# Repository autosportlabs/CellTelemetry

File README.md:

CellTelemetry
=============

Realtime telemetry module for RaceCapture/Pro

http://www.autosportlabs.net/RaceCapture

See the License.txt file for more information on Licensing for this software.

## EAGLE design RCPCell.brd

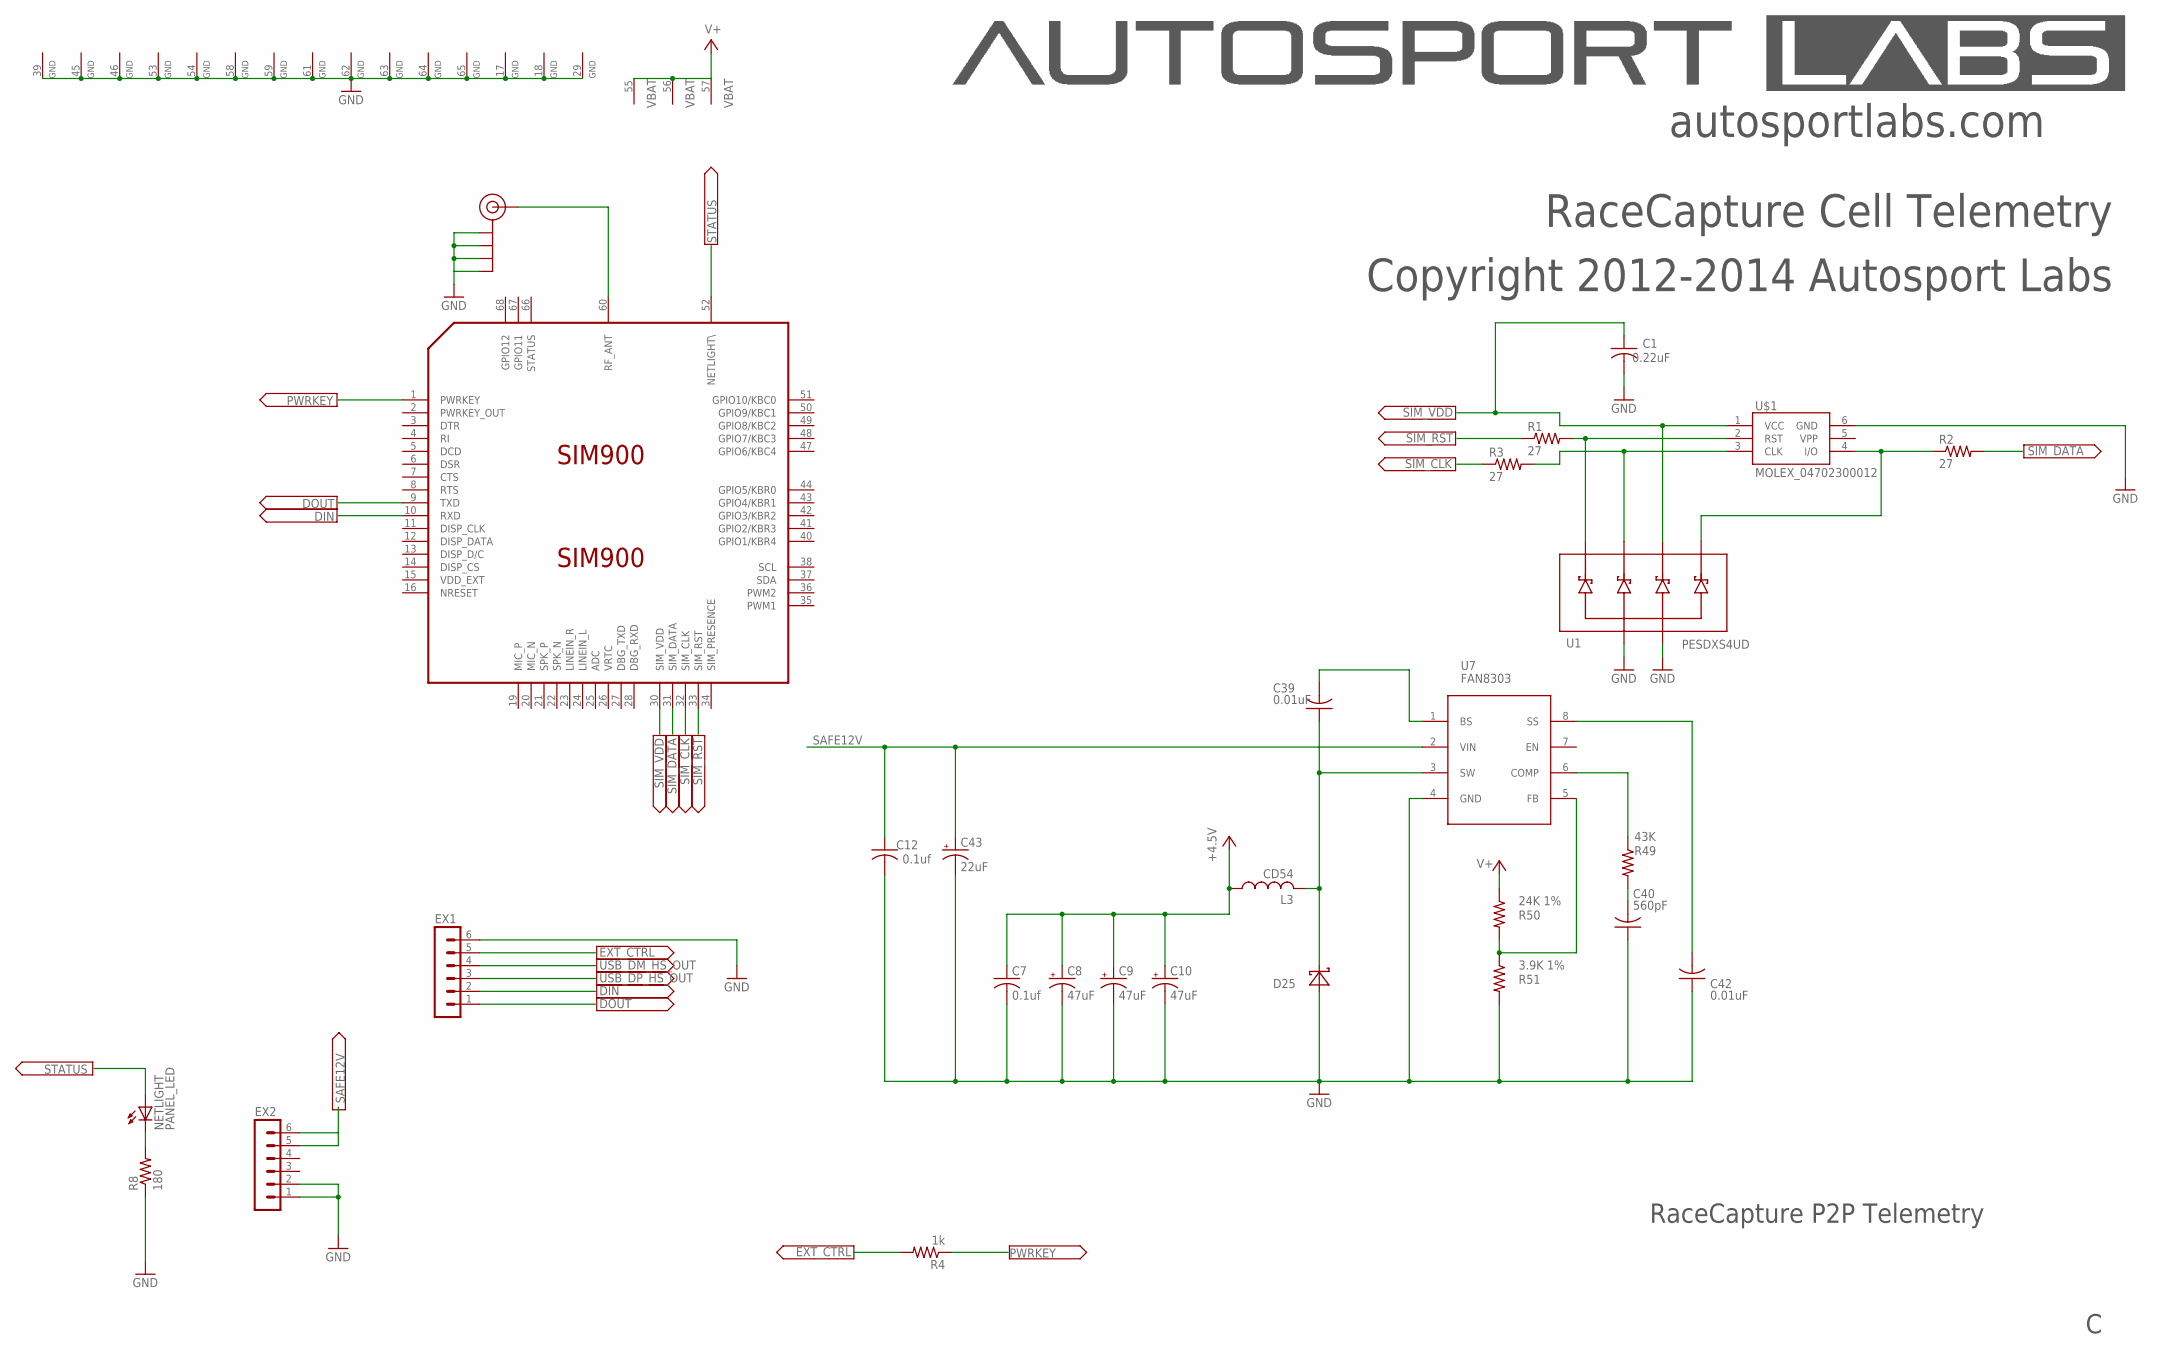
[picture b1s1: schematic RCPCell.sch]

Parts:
C1: 0.22uF; C0603
C7, C12: 0.1uf; C0603
C8, C9, C10: 47uF; SMC_D
C39, C42: 0.01uF; C0603
C40: 560pF; C0603
C43: 22uF; 153CLV-0605
D25: SCHOTTKY; SMA
EX1, EX2: MA06-1
J$1: SMA_EDGE; SMA-EDGE
L3: CD54
NETLIGHT: PANEL_LED; RIGHTANGLE_CML_5323F5
R1, R2, R3: 27; 0603
R4: 1k; 0603
R8: 180; 0603
R49: 43K; R0603
R50: 24K 1%; R0603
R51: 3.9K 1%; R0603
SIM900: SIM900
U1: PESDXS4UD; SC-74
U7: FAN8303; SO-8
U$1: MOLEX_04702300012; MOLEX_91228-3001

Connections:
DIN: EX1.2, SIM900.10 (RXD)
DOUT: EX1.1, SIM900.9 (TXD)
EXT_CTRL: EX1.5, R4.2
GND: C1.2, C7.2, C8.-, C9.-, C10.-, C12.2, C40.1, C42.1, C43.-, D25.A, EX1.6, EX2.1, EX2.2, J$1.GND@0 (GND), J$1.GND@1 (GND), J$1.GND@2 (GND), J$1.GND@3 (GND), R8.1, R51.2, SIM900.17 (GND), SIM900.18 (GND), SIM900.29 (GND), SIM900.39 (GND), SIM900.45 (GND), SIM900.46 (GND), SIM900.53 (GND), SIM900.54 (GND), SIM900.58 (GND), SIM900.59 (GND), SIM900.61 (GND), SIM900.62 (GND), SIM900.63 (GND), SIM900.64 (GND), SIM900.65 (GND), U1.2, U1.5, U7.4 (GND), U$1.6 (GND)
unnamed: NETLIGHT.C, R8.2
unnamed: R50.2, R51.1, U7.5 (FB)
unnamed: C39.2, U7.1 (BS)
unnamed: C39.1, D25.C, L3.P$2 (2), U7.3 (SW)
unnamed: C40.2, R49.2
unnamed: R49.1, U7.6 (COMP)
unnamed: C42.2, U7.8 (SS)
PWRKEY: R4.1, SIM900.1 (PWRKEY)
RF_ANT: J$1.SIG (SIGNAL), SIM900.60 (RF_ANT)
SAFE12V: C12.1, C43.+, EX2.5, EX2.6, U7.2 (VIN)
SIM_CLK: R3.1, SIM900.32 (SIM_CLK)
SIM_CLK_CARD: R3.2, U1.3, U$1.3 (CLK)
SIM_DATA: R2.2, SIM900.31 (SIM_DATA)
SIM_DATA_CARD: R2.1, U1.6, U$1.4 (I/O)
SIM_RST: R1.1, SIM900.33 (SIM_RST)
SIM_RST_CARD: R1.2, U1.1, U$1.2 (RST)
SIM_VDD: C1.1, SIM900.30 (SIM_VDD), U1.4, U$1.1 (VCC)
STATUS: NETLIGHT.A, SIM900.52 (NETLIGHT\)
USB_DM_HS_OUT: EX1.4
USB_DP_HS_OUT: EX1.3
V+: C7.1, C8.+, C9.+, C10.+, L3.P$1 (1), R50.1, SIM900.55 (VBAT), SIM900.56 (VBAT), SIM900.57 (VBAT)

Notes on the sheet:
RaceCapture P2P Telemetry
Copyright 2012-2014 Autosport Labs
RaceCapture Cell Telemetry
autosportlabs.com

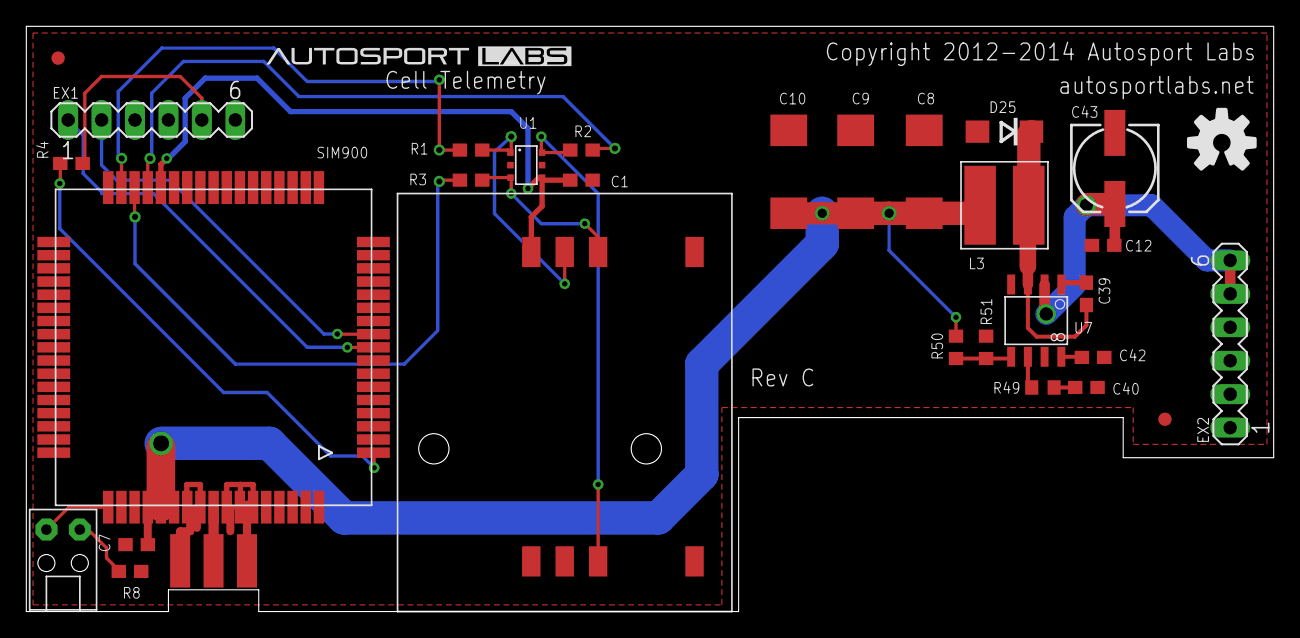
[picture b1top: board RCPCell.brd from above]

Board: 2 copper layers, 94.7 x 44.5 mm, 28 parts (0 on the bottom side), 23 nets.

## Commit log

2012-08-18 added Cellular telemetry module
2012-08-18 added current limiting resistors to TVS circuit
2012-08-18 final update before expert review
2012-08-19 changed design around SMA connector, designe for 50 ohms at 900MHz
2013-03-14 updates to final RCP cell device
2013-03-14 updated cellular module with additional RX-TX LEDs, new simcard holder, removed STATUS light b/c not functional on SIM900
2013-03-14 bumped to RevB
2013-04-01 revision b for production
2013-05-29 added License file
2013-05-29 added readme file
2014-06-02 WIP for MK2 cell module
2014-06-02 placeholder simcard
2014-06-02 added ejector simcard holder
2014-06-02 moving lbr to common location
2014-06-02 WIP for MK2 version of cell module
2014-06-02 WIP for cellular module, compacted board size
2014-06-02 modified notch to account for bit radius
2014-06-02 final layout before incorporating power supply section
2014-06-02 exported updated image; moved revision tag
2014-06-03 laid out power supply section, fixed DRC errors
2014-06-03 tentative final version of RevC module
2014-06-03 yak shaving design a bit
2014-09-11 WIP for flipping cell module components over
2014-09-12 flipped components on cell module to top side
2014-09-12 updated screenshot
2014-09-12 made sma slot notch more narrow
2014-09-12 adjusted ground plane
2014-09-12 widened simcard vdd trace
2014-09-12 removed label which had no room, fixed line thickness
2014-09-12 fixed label
2014-10-17 fixed flipped routing on I/O header
2014-10-17 added fiducial marks; fixed missing dimension line
2014-11-01 added BOM and board image
